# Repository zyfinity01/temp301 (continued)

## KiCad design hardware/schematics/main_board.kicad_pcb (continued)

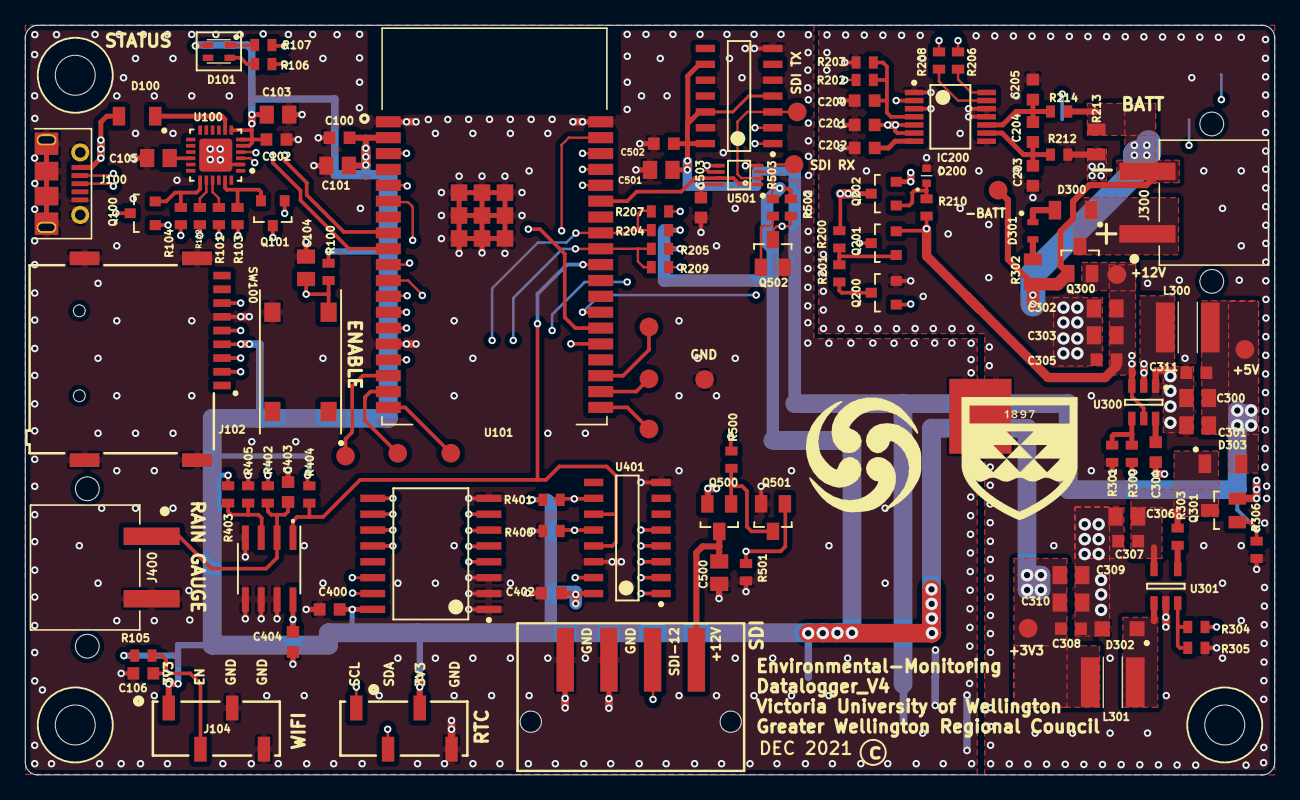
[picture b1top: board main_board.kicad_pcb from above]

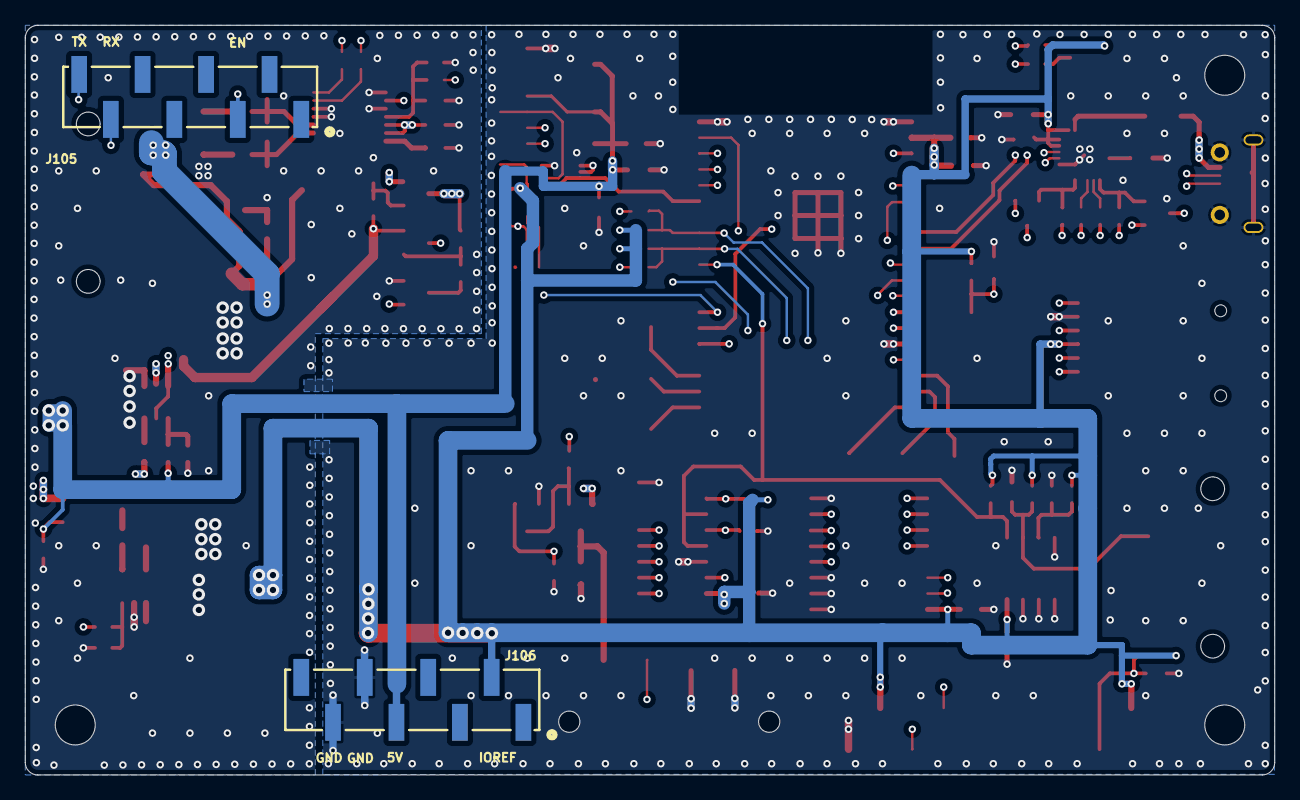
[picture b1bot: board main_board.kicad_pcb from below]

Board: 4 copper layers, 100.0 x 60.0 mm, 128 parts (2 on the bottom side), 87 nets.

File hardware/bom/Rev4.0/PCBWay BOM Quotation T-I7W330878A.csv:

"PCBWay Bom Quotation, Product No.:T-I7W330878A",,,,,,,,,,,,,,
Item #,*Designator,*Qty,Manufacturer,*Mfg Part #,Description / Value,*Package/Footprint,Your Instructions / Notes,*Unit Price(5 sets),*Total,*Delivery Time,*Actual Purchase Mfg Part #,*PCBWay Note,Customer Reply,PCBWay Update
1,"C100,C102,C106,C305,C307,C308,C502",7,Yageo,CC0603KRX5R8BB104,100nF,OPL_Capacitor:C0603,,$0.240,$8.400,,,,,
2,"C101,C103,C104,C105,C302,C303,C501",7,Yageo,CC0805KKX5R8BB106,10uF,OPL_Capacitor:C0805,,$0.080,$2.800,,,,,
3,C200,1,Yageo,CC0603KRX7R8BB332,3.3nF,OPL_Capacitor:C0603,,$0.160,$0.800,,,,,
4,"C201,C204,C402,C403,C404",5,Yageo,CC0603KRX5R8BB104,100nF,OPL_Capacitor:C0603,,$0.240,$6.000,,,,,
5,C202,1,Yageo,CC0603KRX6S8BB105,1uF,OPL_Capacitor:C0603,,$0.240,$1.200,,,,,
6,"C203,C205,C304",3,Yageo,CC0603KRX5R8BB104,100nF,OPL_Capacitor:C0603,,$0.240,$3.600,,,,,
7,"C300,C301,C306,C309,C310",5,Yageo,CC0805MKX5R8BB226,22uF,OPL_Capacitor:C0805,,$0.480,$12.000,,,,,
8,"C311,C503",2,Yageo,CC0603KRX5R8BB104,100uF,OPL_Capacitor:C0603,,$0.240,$2.400,,,,,
9,C400,1,Yageo,CC0603KRX5R8BB104,100nF,OPL_Capacitor:C0603,,$0.240,$1.200,,,,,
10,C500,1,Yageo,CC0805MKX5R8BB226,22uF,OPL_Capacitor:C0805,,$0.480,$2.400,,,,,
11,D100,1,Diodes Incorporated,1N5819HW1-7-F,1N5819HW1-7-F,Diode_SMD:D_SMA,,$0.407,$2.035,,,,,
12,D101,1,Kingbright,APTF1616SEEZGQBDC,RGBLED,,,$0.708,$3.540,,,,,
13,D200,1,Diodes Incorporated,BZT52C5V6T-7,BZT52C5V6T-7,,,$0.272,$1.360,7-10 Workdays,,,,
14,D300,1,Diodes Incorporated,1N5819HW1-7-F,1N5819HW1-7-F,Diode_SMD:D_SMA,,$0.407,$2.035,,,,,
15,D301,1,,19-217-R6C-AL1M2VY-3T,RED_LED,LED_SMD:LED_0603_1608Metric,Put any Red led that match the footprint,$0.452,$2.260,,,,,
16,D302,1,Toshiba Semiconductor and Storage,CRS08,CRS08,SODFL3500X98N,,$0.708,$3.540,,,,,
17,D303,1,Diodes Incorporated,1N5819HW1-7-F,1N5819HW1-7-F,Diode_SMD:D_SMA,,$0.407,$2.035,,,,,
18,IC200,1,Texas Instruments,BQ34Z110PWR,BQ34Z110PWR,SOP65P640X120-14N,,$9.072,$45.360,7-10 Workdays,,,,
19,J100,1,Molex,1050170001,USB_B_Micro,CON_1050170001,,$0.407,$2.035,,,,,
20,J102,1,GCT,MEM2075-00-140-01-A,SDCARD,,,$2.631,$13.155,7-10 Workdays,,,,
21,J103,1,,NPTC041KFXC-RC,I2C,,,$0.708,$3.540,,,,,
22,J104,1,,NPTC041KFXC-RC,WIFI_EN,,,$0.708,$3.540,,,,,
23,J105,1,Molex,878980826,MODEM_A,,Connector,$2.470,$12.350,7-10 Workdays,87898-0826,,,
24,J106,1,Molex,878980826,MODEM_B,,Connector,$2.470,$12.350,7-10 Workdays,87898-0826,,,
25,J300,1,W黵th Elektronik,691508110302,BATT,,Connector,$4.793,$23.965,7-10 Workdays,691709710302,,,
26,J400,1,W黵th Elektronik,691508110302,Grain_gauge,,Connector,$4.793,$23.965,7-10 Workdays,691709710302,,,
27,J500,1,W黵th Elektronik,691508110304,SDI-12,,Connector,$5.040,$25.200,,,,,
28,"L300,L301",2,Bourns Inc.,SRN5040-4R7M,4.7uH,SRN5040-4R7M:INDPM5050X400N,,$0.484,$4.840,,,,,
29,"MH100,MH101,MH103",3,,M3,${TOPCODE},,Though holes,,,,,[DNP];,,
30,Q100,1,Diodes Incorporated,BC847A-7-F,BC847,Package_TO_SOT_SMD:SOT-23,,$0.407,$2.035,,,,,
31,Q101,1,Diodes Incorporated,BC847A-7-F,BC847,Package_TO_SOT_SMD:SOT-23,,$0.407,$2.035,,,,,
32,Q200,1,ON Semiconductor,2N7002NCT-ND,2N7002,Package_TO_SOT_SMD:SOT-23,,$0.126,$0.630,,2N7002,The part we will supply is made by  Slkor,,
33,Q201,1,ON Semiconductor,BSS84CT-ND,BSS84,Package_TO_SOT_SMD:SOT-23,,$0.138,$0.690,,BSS84,The part we will supply is made by  Slkor,,
34,Q202,1,ON Semiconductor,2N7002NCT-ND,2N7002,Package_TO_SOT_SMD:SOT-23,,$0.126,$0.630,,2N7002,The part we will supply is made by  Slkor,,
35,Q300,1,ON Semiconductor,FDN360P,FDN360P,OPL_Discrete_Semiconductor:SOT-23,,$1.248,$6.240,,,,,
36,Q301,1,ON Semiconductor,FDN360P,FDN360P,OPL_Discrete_Semiconductor:SOT-23,,$1.248,$6.240,,,,,
37,Q500,1,ON Semiconductor,FDN360P,FDN360P,OPL_Discrete_Semiconductor:SOT-23,,$1.248,$6.240,,,,,
38,Q501,1,ON Semiconductor,FDN361BN,FDN361BN,OPL_Discrete_Semiconductor:SOT-23,,$0.720,$3.600,15 Workdays,,,,
39,Q502,1,ON Semiconductor,FDN361BN,FDN361BN,OPL_Discrete_Semiconductor:SOT-23,,$0.720,$3.600,15 Workdays,,,,
40,"R100,R306",2,Yageo,RC0603FR-0710KL,10K,OPL_Resistor:R0603,,$0.011,$0.110,,,,,
41,"R101,R102",2,Yageo,RC0603FR-07470RL,470,OPL_Resistor:R0603,,$0.016,$0.160,,,,,
42,"R103,R104",2,Yageo,RC0603FR-0710KL,10K,OPL_Resistor:R0603,,$0.011,$0.110,,,,,
43,"R105,R204,R205,R301,R305,R400,R401,R402,R403,R404",10,Yageo,RC0603FR-0710KL,10K,OPL_Resistor:R0603,,$0.011,$0.550,,,,,
44,"R106,R107",2,Yageo,RC0603FR-07100RL,100,OPL_Resistor:R0603,,$0.013,$0.130,,,,,
45,R200,1,Yageo,RC0603FR-10100KL,100K,OPL_Resistor:R0603,,$0.088,$0.440,,,,,
46,R201,1,Yageo,RC0603FR-07165KL,165K,OPL_Resistor:R0603,,$0.088,$0.440,,,,,
47,R202,1,Yageo,RC0603FR-07300KL,300K,OPL_Resistor:R0603,,$0.033,$0.165,,,,,
48,R203,1,Yageo,RC0603DR-0716K5L,16K5,OPL_Resistor:R0603,,$0.088,$0.440,,,,,
49,"R206,R207,R208,R209,R212,R214",6,Yageo,RC0603FR-07100RL,100,OPL_Resistor:R0603,,$0.013,$0.390,,,,,
50,R210,1,Yageo,RC0603FR-1010KL,10K,OPL_Resistor:R0603,,$0.088,$0.440,,,,,
51,R213,1,Yageo,PE0805DRF7W0R1L,0.1,OPL_Resistor:R0805,,$1.000,$5.000,,,,,
52,R300,1,Yageo,RC0603FR-0756KL,56K,OPL_Resistor:R0603,,$0.032,$0.160,,,,,
53,R302,1,Yageo,RC0805FR-073K3L,3K3,OPL_Resistor:R0805,,$0.055,$0.275,,,,,
54,R303,1,Yageo,RC0603FR-10100KL,100K,OPL_Resistor:R0603,,$0.088,$0.440,,,,,
55,R304,1,Yageo,RC0603FR-0745K3L,5K3,OPL_Resistor:R0603,,$0.033,$0.165,,,,,
56,R405,1,Yageo,RC0603FR-074K7L,4K7,OPL_Resistor:R0603,,$0.028,$0.140,,,,,
57,"R500,R501,R502",3,Yageo,RC0603JR-071ML,1M,OPL_Resistor:R0603,,$0.007,$0.105,,,,,
58,R503,1,Yageo,RC0603JR-070RL,0,OPL_Resistor:R0603,,$0.021,$0.105,,,,,
59,SP200,1,,*,${TOPCODE},,Bridge,,,,,[DNP];,,
60,SW100,1,CIT Relay and Switch,CS11025.0F160,Push_Button,OPL_Switch:SW4-SMD-6.0X6.0X5.0MM,,$0.348,$1.740,7-10 Workdays,,,,
61,"TP100,TP101,TP103",3,,RevPol,RevPol,Connector_Pin:Pin_D1.0mm_L10.0mm,Test point,,,,,[DNP];,,
62,"TP102,TP104,TP105,TP106,TP301,TP304",6,,RevPol,RevPol,Connector_Pin:Pin_D1.0mm_L10.0mm,Test point,,,,,[DNP];,,
63,TP300,1,,5V,5V,Connector_Pin:Pin_D1.0mm_L10.0mm,Test point,,,,,[DNP];,,
64,TP302,1,,3V3,3V3,Connector_Pin:Pin_D1.0mm_L10.0mm,Test point,,,,,[DNP];,,
65,TP501,1,,SDI_Tx,SDI_Tx,,Test point,,,,,[DNP];,,
66,TP502,1,,SDI_Rx,SDI_Rx,,Test point,,,,,[DNP];,,
67,U100,1,Silicon Labs,CP2104-F03-GM,CP2104,Package_DFN_QFN:QFN-24-1EP_4x4mm_P0.5mm_EP2.6x2.6mm,,$4.584,$22.920,,,,,
68,U101,1,Espressif Systems,ESP32-WROVER-B (8MB),ESP32-WROVER-B,esp32-wrover:ESP32-WROVER,,$9.480,$47.400,,,Price may increase after you place the order due to the worldwide components shortage. Plz confirm asap.Or you can supply this part to us for assembly,,
69,U300,1,Texas Instruments,TPS562201DDCR,TPS562201DDCR,Package_TO_SOT_SMD:SOT-23-6,,$1.085,$5.425,,,,,
70,U301,1,Texas Instruments,LM2831XMF,LM2831XMF,SOT95P280X145-5N,,$3.240,$16.200,,LM2831XMF/NOPB,,,
71,U400,1,Texas Instruments,PCF8574ADGVR,PCF8574ADWR,,,$2.553,$12.765,7-10 Workdays,,,,
72,U401,1,Nexperia USA Inc.,"74HC590D,118","74HC590D,118",SOIC127P600X175-16N:SOIC127P600X175-16N,,$0.801,$4.005,7-10 Workdays,,,,
73,U402,1,Texas Instruments,LM393-N,LM393-N,,,$2.216,$11.080,7-10 Workdays,LM393N/NOPB,,,
74,U500,1,Texas Instruments,SN74LS00DR,SN74LS00DR,Package_SO:SOIC-14_3.9x8.7mm_P1.27mm,,$0.816,$4.080,,,,,
75,U501,1,Texas Instruments,SN74LVC2G241DCUR,SN74LVC2G241DCUR,Package_SO:VSSOP-8_2.3x2mm_P0.5mm,,$0.538,$2.690,,,,,
76,,5,Silicon Labs,SI7201-B-09-IB,"Sensor, Hall effect",,buy but not assembly ,$2.168,$54.200,7-10 Workdays,,,,
,,,,,,,,component price ,$452.115,,,,,
,,,,,,,,assembly price ,$88.000,,,,,
,,,,,,,,board price ,$54.480,,,,,
,,,,,,,,,,,,,,
,,,,,,,,,,,,,,
,,,,,,,,,,,,,,

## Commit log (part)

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2023-04-06 refactor(rain-gauge): Made Change to check schedule for if raining
2023-04-11 fix(webapp): remove azure references
2023-04-12 feat(webapp): Added toggle to show and hide password.
2023-04-12 fix(webapp): Removed trailing whitespace.
2023-04-16 refactor(services): implement the Sdi12 config
2023-04-16 refactor(services): implement the mmwconfig config
2023-04-17 refactor(services): implement the MqttConfig
2023-04-18 refactor(services): implement the DataConfig
2023-05-03 feat(sdcard): Implement debug failed transmission writing on network failure
    Currently does not save to an actual file, but logs the save event in the log output. Allows for the sd card to be absent, but warns that failed transmissions will be lost
2023-05-03 feat(sdcard): Implement cache to 'failed_transmissions/' on network failure
2023-05-03 fix(sdcard): Fix compat with f-strings
    Removed f-strings as they are not supported by the version of micropython being used
2023-05-03 fix(sdcard): Fix leading f-tag
2023-05-03 feat(sdcard): Implement warning for overriding existing cached failed transmission
2023-05-03 refactor(network): Adding correct link for webhook
2023-05-03 refactor(rain-gauge): set should send when raining to 5min and if not raining 1 hour
2023-05-04 chore(rain-gauge): Added constants for FIVE_MINUTES and SIXTY_MINUTES
2023-05-04 feat(sdcard): Add method for loading in failed transmission data
2023-05-04 perf(sdcard): Change read_failed_transmission() to utilise os.scandir()
    os.scandir() generates a generator object, allowing for iteration of the directory without loading the entire file list into memory. This is important due to the limitations of the ESP32. This improv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
2023-05-04 feat(sdcard): Implement safety check to ensure SD card is mounted before loading cached recording files
2023-05-04 refactor(rain-gauge): compressed rainfall function
2023-05-04 refactor(sdcard): Update read function to pull from csv cache file
2023-05-04 feat(sdcard): Add function for removing latest entry from failed-transmissions cache
2023-05-09 perf(sdcard): Change failed transmission cache operations to dynamicly load data
    Instead of loading the entire file into memory, the cache now utilises f.seek() to traverse and navigate to the specific required index. This helps to avoid loading and mutating the entire file withi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
2023-05-09 refactor(network): Delambdafy the transmit function
    Lambdas were not required, and the same effect could be achieved more readably with if/else branching
2023-05-09 refactor(network): Implement catchup routine for failed transmissions
    The new implementation involved utilising callback lambdas in the event of success or failure, allowing the process to be much more generic
2023-05-09 refactor(network): Place transmission phase into helper method
2023-05-09 build(webapp): water history page, input refers to the created history/index.ts file
2023-05-09 build(webapp): water history page, refers to the button for the history page within the main webapp ui
2023-05-09 build(webapp): water history page, refers to creation base style
2023-05-09 style(webapp): Fix trailing whitespace on history index page
2023-05-09 fix(webapp): history tab shows water level history
2023-05-10 build(webapp): fix maintenance mode bug
2023-05-10 test(network): Added testing publish for mqqt sending to mattermost
2023-05-11 refactor(services): refactor as requested in todo
2023-05-11 fix(network): Fix scoping issues with modem variable
2023-05-11 fix(sdcard): Add check to ensure existance of resend cache file
2023-05-11 chore(drivers): Fix sdcard.py formatting
2023-05-15 fix(sdcard): Replace os constants with integer constants
2023-05-15 fix(sdcard): Refactor deleting of transmitted cache to avoid use of ftruncate()
    Micropython does not support file truncations. This new implementation instead reads and writes each line into a new file, skipping the last line. See https://github.com/micropython/micropython/issue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
2023-05-15 style(network): Fix issue with black formatting
2023-05-16 feat(webapp): filteration functionality implemented in history page
2023-05-16 build(webapp): create new file for getting data
2023-05-16 fix(webapp): Precommit build issue fixed
2023-05-16 feat(webapp): Added filter functionality in History Page
2023-05-16 feat(services): return data with correct types
2023-05-16 fix(services): correct import statements
2023-05-16 fix(services): ensure compatibility for a single CSV file instead of a stream.
2023-05-17 build(webapp): adding new drop-down menu select
2023-05-17 docs(sdi-12): Created docs/research directory, containing file to document sdi-12 research
2023-05-17 docs(sdi-12): added script we used in repl loop to query addresses of sensors on sdi-12 line
2023-05-17 build(webapp): updating so default graph shows precipitation data
2023-05-17 fix(services): reading from a csv file works now
2023-05-17 fix(services): add empty line at the end of watershed.js
2023-05-18 fix(services): return correct types from csv
2023-05-18 feat(rtc): good commit
2023-05-19 fix(webapp): resize popup window to better fit content
2023-05-19 refactor(services): add a default dictionary within BaseConfig
2023-05-19 refactor(services): fix up default config, implement comparison between default and old
2023-05-20 fix(services): save the json config with indentation
2023-05-20 feat(services): save the baseconfig after changes
2023-05-20 feat(services): added save param to MmwSettings
2023-05-20 feat(services): add save to MqttConfig
2023-05-20 feat(services): use the save method in MqttConfig
2023-05-20 feat(services): use save method in Sdi12Config
2023-05-20 fix(services): remove incorrect water_sensor definition from BaseConfig
2023-05-20 feat(services): use save method in WaterSensorConfig
2023-05-20 feat(services): use save method in ReadingsConfig
2023-05-20 feat(services): add save method to DataConfig
2023-05-20 feat(services): use the save method in DataConfig
2023-05-20 feat(webapp): Create the inital typeScript file dark_mode_toggle.tsx which holds the main implementation for switching from light to dark mode.
2023-05-20 feat(webapp): Create the inital typeScript file dark_mode_toggle.tsx which holds the main implementation for switching from light to dark mode. Fixed issues relating to the lint pipelines.
2023-05-23 feat(webapp): merge issue fixed
2023-05-23 docs(battery): created a file and filled with outline headers for battery fuel gauge retrospective
2023-05-23 fix(webapp): Fix Graph Display Duplication
2023-05-23 feat(sdi-12): Added transint protection into the sdi-12 schematic, saved as a aseperate schematic. Included and explanation with links to example schematic in /docs.
2023-05-24 feat(sdi-12): The spark gap drawing to add to the schematic is now added to our kicad library as spark_gap
2023-05-24 docs(battery): added writeup as to why we couldn't implement the battery fuel gauge
2023-05-24 docs(sdi-12): moved sdi12-investigation.md writup from docs/research to docs/technical
2023-05-24 chore(repo): Move transient_schemtic_docs.md to docs/technical directory
2023-05-24 docs(battery): Added to the BatteryFuelGaugeRetrospective
2023-05-24 refactor(services): convert test_modem to new config
2023-05-24 fix(services): fix formatting of test_modem
2023-05-25 test(rtc): Recommit as last failed pipeline
2023-05-25 test(rtc): Recommit as last failed pipeline again
2023-05-25 refactor(modem): Fixed regex for on_off_switch method
2023-05-25 build(webapp): adding button for modem on/off, design only - no direct functionality implemented
2023-05-27 feat(sdi-12): added the address query command as a constant
2023-05-27 feat(webapp): Light and Dark mode UX fully implemented. In this commit, I implemented the styling for the Enable Maintenance Mode Pop up and the Add SDI-12 Sensor Pop Up. This issue and branch is now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
2023-05-27 feat(sdi-12): added the address query command as variable
2023-05-29 fix(webapp): update preact for node 16.16.0
2023-05-29 fix(webapp): update preact-cli for node 16.16.0
2023-05-29 fix(webapp): notyf updated to v3.10.0
2023-05-29 fix(webapp): sirv-cli updated v1.0.14
2023-05-29 fix(webapp): typescript updated v3.9.10
2023-05-29 refactor(rtc): Moved debug statement from regular mode to pipeline scheduler
2023-05-29 docs(rtc): Removed Redundent code FIXME from regular mode
2023-05-30 feat(webapp): Created the login and register jsx files and have imported them into app.tsx.
2023-05-30 feat(webapp): Added the form and input boxes for the log in form and connected to the functionality using preacts useState.
2023-05-30 feat(webapp): Fixing End of Files error from the previous commit to pass the lint pipeline.
2023-05-30 feat(sdi-12): editing the sdi-12investigation.md
2023-05-30 feat(sdi-12): removing sdi-12investigation.md as it is on the wrong branch
2023-05-30 fix(sdi-12): added fix to unaddressed command function
2023-05-31 docs(services): Added Section to the util README for the recently added discord bot
2023-05-31 docs(sdi-12): Completed SDI12 evaluation of the hardware
2023-05-31 fix(services): declare encoding on saving the config
2023-05-31 fix(services): fix formatting on new config
2023-06-01 test(rtc): Add test_timezone() method
2023-06-01 refactor(requirements): Adding first implementation for sending straight to mattermost
2023-06-01 style(requirements): Running Precommit on my laptop
2023-06-01 refactor(requirements): Setting up http connections with https to mattermost
2023-06-01 fix(rtc): Imported missing import (utime)
2023-06-01 fix(rtc): Imported missing import (utime), blacked
2023-06-01 refactor(device-sw): refactored regular mode to remove redundant code and comments to improve readability
2023-06-01 test(sdcard): Implement manual io speed test for SD card
2023-06-01 build(webapp): adjusting inputs to match data.json config file
2023-06-01 refactor(services): Update config.new to have defaults
2023-06-01 feat(repo): added source code for discord bot integration
2023-06-01 fix(services): moved discord.py to utility
2023-06-02 build(webapp): typescript upgraded 5.0.4 --> 5.1.3
2023-06-02 fix(services): corrected modem unit test names, and added return to modem power_off
2023-06-02 refactor(webapp): Improved structure
2023-06-02 fix(webapp): handle API fetch errors in refactored code
2023-06-02 test(rtc): Change test_timezone(self) method to give more information
2023-06-02 fix(webapp): revert change
2023-06-02 fix(webapp): position scrollbar to the right so it doesn't overlap data table
2023-06-03 chore(webapp): remove unnecessary code from the header component
2023-06-03 chore(webapp): remove unnecessary code from the monitor component
2023-06-03 chore(webapp): remove unnecessary code from the sensorconfig component
2023-06-03 fix(webapp): babel-config patched to allow md5 use
2023-06-03 fix(webapp): preact-config patched to allow md5 use
2023-06-03 chore(webapp): remove unnecessary code from the main app component
2023-06-03 chore(webapp): remove unnecessary code from the util component
2023-06-03 chore(webapp): remove unnecessary code that was missed
2023-06-03 fix(webapp): dev_environment_setup doc updated.
2023-06-03 fix(webapp): pipeline issue with indentation fixed
2023-06-03 build(webapp): updated prettier to next major patch 1.19.1 -> 2.0.0
2023-06-03 build(webapp): eslint-plugin-react-hooks updated major patch 3.0.0 -> 4.0.0
2023-06-03 refactor(device-sw): configure mode to remove redundant code and comments to improve readability
2023-06-03 build(webapp): update lint-staged to latest 10.5.4 -> 13.2.2
2023-06-03 build(webapp): update jest to latest 24.9.0 -> 29.5.0
2023-06-03 build(webapp): update @types/jest to latest 25.2.3 -> 29.5.2
2023-06-03 build(webapp): update enzyme-adapter-preact-pure to latest 2.3.0 -> 4.1.0
2023-06-03 build(webapp): updated reactjs-popup 1.5.0 -> 2.0.5
2023-06-03 fix(webapp): pulled commits from main
2023-06-03 refactor(rtc): imported utime instead of time to improve resource usage efficiency
2023-06-04 fix(webapp): fixed default css bug with updating reactjs-popup
2023-06-04 build(webapp): react-hook-form 6.15.8 to 7.44.3
2023-06-04 build(webapp): react-hook-form update issue fixed
